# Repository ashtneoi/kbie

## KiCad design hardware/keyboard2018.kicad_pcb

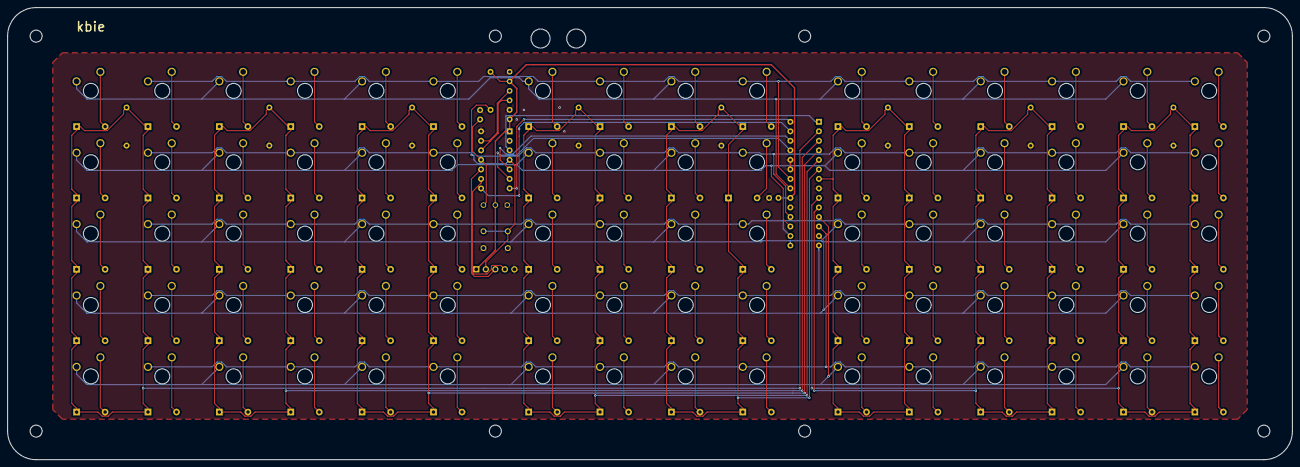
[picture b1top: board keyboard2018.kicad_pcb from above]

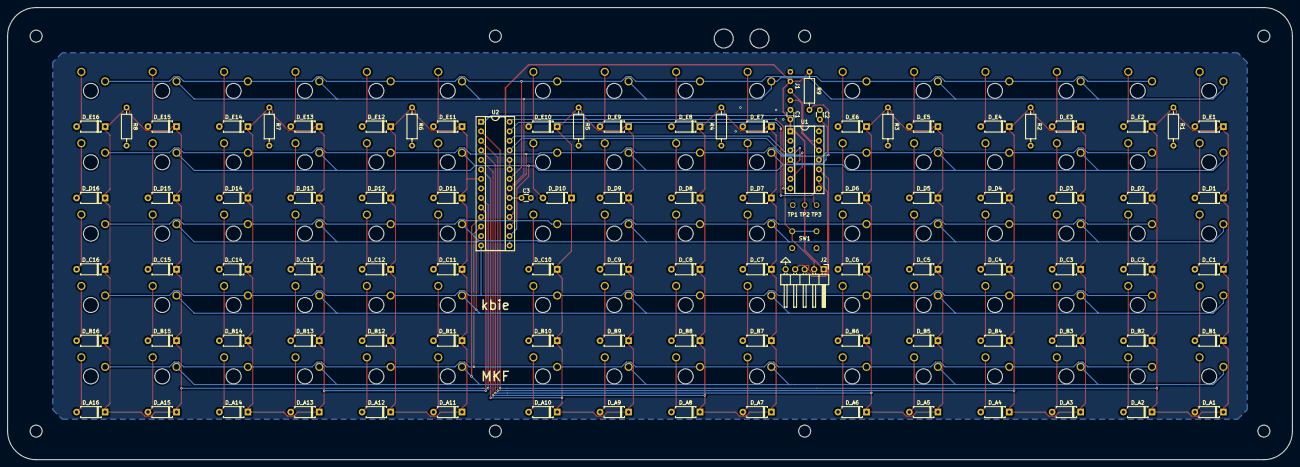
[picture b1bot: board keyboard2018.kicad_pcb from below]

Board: 2 copper layers, 342.9 x 120.7 mm, 180 parts (99 on the bottom side), 111 nets.

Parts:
C1, C3: 100n; C_Disc_D3.0mm_W1.6mm_P2.50mm
C2: 470n; C_Disc_D3.0mm_W1.6mm_P2.50mm
D_A1, D_A2, D_A3, D_A4, D_A5, D_A6, D_A7, D_A8, D_A9, D_A10, D_A11, D_A12, D_A13, D_A14, D_A15, D_A16: D; D_A-405_P7.62mm_Horizontal
D_B1, D_B2, D_B3, D_B4, D_B5, D_B6, D_B7, D_B8, D_B9, D_B10, D_B11, D_B12, D_B13, D_B14, D_B15, D_B16: D; D_A-405_P7.62mm_Horizontal
D_C1, D_C2, D_C3, D_C4, D_C5, D_C6, D_C7, D_C8, D_C9, D_C10, D_C11, D_C12, D_C13, D_C14, D_C15, D_C16: D; D_A-405_P7.62mm_Horizontal
D_D1, D_D2, D_D3, D_D4, D_D5, D_D6, D_D7, D_D8, D_D9, D_D10, D_D11, D_D12, D_D13, D_D14, D_D15, D_D16: D; D_A-405_P7.62mm_Horizontal
D_E1, D_E2, D_E3, D_E4, D_E5, D_E6, D_E7, D_E8, D_E9, D_E10, D_E11, D_E12, D_E13, D_E14, D_E15, D_E16: D; D_A-405_P7.62mm_Horizontal
J1: USB_B_no_shield; captive USB
J2: Conn_01x05_Male; PinHeader_1x05_P2.54mm_Horizontal
R1, R2, R3, R4, R5, R6, R7, R8: 1k; R_Axial_DIN0207_L6.3mm_D2.5mm_P10.16mm_Horizontal
R9: 10k; R_Axial_DIN0207_L6.3mm_D2.5mm_P10.16mm_Horizontal
SW1: SW_Push; TE FSM4JAH
SW_A1, SW_A2, SW_A3, SW_A4, SW_A5, SW_A6, SW_A7, SW_A8, SW_A9, SW_A10, SW_A11, SW_A12, SW_A13, SW_A14, SW_A15, SW_A16: SW_Push; SW_Cherry_MX1A_1.00u_Plate_with_mounting_hole
SW_B1, SW_B2, SW_B3, SW_B4, SW_B5, SW_B6, SW_B7, SW_B8, SW_B9, SW_B10, SW_B11, SW_B12, SW_B13, SW_B14, SW_B15, SW_B16: SW_Push; SW_Cherry_MX1A_1.00u_Plate_with_mounting_hole
SW_C1, SW_C2, SW_C3, SW_C4, SW_C5, SW_C6, SW_C7, SW_C8, SW_C9, SW_C10, SW_C11, SW_C12, SW_C13, SW_C14, SW_C15, SW_C16: SW_Push; SW_Cherry_MX1A_1.00u_Plate_with_mounting_hole
SW_D1, SW_D2, SW_D3, SW_D4, SW_D5, SW_D6, SW_D7, SW_D8, SW_D9, SW_D10, SW_D11, SW_D12, SW_D13, SW_D14, SW_D15, SW_D16: SW_Push; SW_Cherry_MX1A_1.00u_Plate_with_mounting_hole
SW_E1, SW_E2, SW_E3, SW_E4, SW_E5, SW_E6, SW_E7, SW_E8, SW_E9, SW_E10, SW_E11, SW_E12, SW_E13, SW_E14, SW_E15, SW_E16: SW_Push; SW_Cherry_MX1A_1.00u_Plate_with_mounting_hole
TP1, TP2, TP3: TestPoint; test point 1mm
U1: PIC16F1454-IP; DIP-14_W7.62mm_Socket
U2: PIC16F18855-IP; DIP-28_W7.62mm_Socket

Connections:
/COL1: D_A1.1, D_A2.1, D_B1.1, D_B2.1, D_C1.1, D_C2.1, D_D1.1, D_D2.1, D_E1.1, D_E2.1, R1.1, U2.2
/COL2: D_A3.1, D_A4.1, D_B3.1, D_B4.1, D_C3.1, D_C4.1, D_D3.1, D_D4.1, D_E3.1, D_E4.1, R2.1, U2.3
/COL3: D_A5.1, D_A6.1, D_B5.1, D_B6.1, D_C5.1, D_C6.1, D_D5.1, D_D6.1, D_E5.1, D_E6.1, R3.1, U2.4
/COL4: D_A7.1, D_A8.1, D_B7.1, D_B8.1, D_C7.1, D_C8.1, D_D7.1, D_D8.1, D_E7.1, D_E8.1, R4.1, U2.5
/COL5: D_A9.1, D_A10.1, D_B9.1, D_B10.1, D_C9.1, D_C10.1, D_D9.1, D_D10.1, D_E9.1, D_E10.1, R5.1, U2.6
/COL6: D_A11.1, D_A12.1, D_B11.1, D_B12.1, D_C11.1, D_C12.1, D_D11.1, D_D12.1, D_E11.1, D_E12.1, R6.1, U2.7
/COL7: D_A13.1, D_A14.1, D_B13.1, D_B14.1, D_C13.1, D_C14.1, D_D13.1, D_D14.1, D_E13.1, D_E14.1, R7.1, U2.10
/COL8: D_A15.1, D_A16.1, D_B15.1, D_B16.1, D_C15.1, D_C16.1, D_D15.1, D_D16.1, D_E15.1, D_E16.1, R8.1, U2.9
/D+: J1.3, U1.13
/D-: J1.2, U1.12
/ICSPCLK_EXT: J2.4, U1.9
/ICSPCLK_INT: U1.8, U2.27
/ICSPDAT_EXT: J2.3, U1.10
/ICSPDAT_INT: U1.7, U2.28
/ROW1: SW_A1.2, SW_A3.2, SW_A5.2, SW_A7.2, SW_A9.2, SW_A11.2, SW_A13.2, SW_A15.2, U2.11
/ROW2: SW_A2.2, SW_A4.2, SW_A6.2, SW_A8.2, SW_A10.2, SW_A12.2, SW_A14.2, SW_A16.2, U2.12
/ROW3: SW_B1.2, SW_B3.2, SW_B5.2, SW_B7.2, SW_B9.2, SW_B11.2, SW_B13.2, SW_B15.2, U2.13
/ROW4: SW_B2.2, SW_B4.2, SW_B6.2, SW_B8.2, SW_B10.2, SW_B12.2, SW_B14.2, SW_B16.2, U2.14
/ROW5: SW_C1.2, SW_C3.2, SW_C5.2, SW_C7.2, SW_C9.2, SW_C11.2, SW_C13.2, SW_C15.2, U2.15
/ROW6: SW_C2.2, SW_C4.2, SW_C6.2, SW_C8.2, SW_C10.2, SW_C12.2, SW_C14.2, SW_C16.2, U2.16
/ROW7: SW_D1.2, SW_D3.2, SW_D5.2, SW_D7.2, SW_D9.2, SW_D11.2, SW_D13.2, SW_D15.2, U2.17
/ROW8: SW_D2.2, SW_D4.2, SW_D6.2, SW_D8.2, SW_D10.2, SW_D12.2, SW_D14.2, SW_D16.2, U2.18
/ROW9: SW_E1.2, SW_E3.2, SW_E5.2, SW_E7.2, SW_E9.2, SW_E11.2, SW_E13.2, SW_E15.2, U2.21
/ROW10: SW_E2.2, SW_E4.2, SW_E6.2, SW_E8.2, SW_E10.2, SW_E12.2, SW_E14.2, SW_E16.2, U2.22
/U1_RX: U1.5, U2.26
/U1_TX: U1.6, U2.25
/~MCLR~_EXT: J2.2, R9.2, SW1.1, U1.4
/~MCLR~_INT: U1.3, U2.1
GND: C1.1, C2.1, C3.1, J1.4, J2.5, R1.2, R2.2, R3.2, R4.2, R5.2, R6.2, R7.2, R8.2, SW1.2, TP1.1, U1.2, U1.14, U2.8, U2.19, U2.23, U2.24
unnamed: C2.2, TP3.1, U1.11
unnamed: D_A1.2, SW_A1.1
unnamed: D_A2.2, SW_A2.1
unnamed: D_A3.2, SW_A3.1
unnamed: D_A4.2, SW_A4.1
unnamed: D_A5.2, SW_A5.1
unnamed: D_A6.2, SW_A6.1
unnamed: D_A7.2, SW_A7.1
unnamed: D_A8.2, SW_A8.1
unnamed: D_A9.2, SW_A9.1
unnamed: D_A10.2, SW_A10.1
unnamed: D_A11.2, SW_A11.1
unnamed: D_A12.2, SW_A12.1
unnamed: D_A13.2, SW_A13.1
unnamed: D_A14.2, SW_A14.1
unnamed: D_A15.2, SW_A15.1
unnamed: D_A16.2, SW_A16.1
unnamed: D_B1.2, SW_B1.1
unnamed: D_B2.2, SW_B2.1
unnamed: D_B3.2, SW_B3.1
unnamed: D_B4.2, SW_B4.1
unnamed: D_B5.2, SW_B5.1
unnamed: D_B6.2, SW_B6.1
unnamed: D_B7.2, SW_B7.1
unnamed: D_B8.2, SW_B8.1
unnamed: D_B9.2, SW_B9.1
unnamed: D_B10.2, SW_B10.1
unnamed: D_B11.2, SW_B11.1
unnamed: D_B12.2, SW_B12.1
unnamed: D_B13.2, SW_B13.1
unnamed: D_B14.2, SW_B14.1
unnamed: D_B15.2, SW_B15.1
unnamed: D_B16.2, SW_B16.1
unnamed: D_C1.2, SW_C1.1
unnamed: D_C2.2, SW_C2.1
unnamed: D_C3.2, SW_C3.1
unnamed: D_C4.2, SW_C4.1
unnamed: D_C5.2, SW_C5.1
unnamed: D_C6.2, SW_C6.1
unnamed: D_C7.2, SW_C7.1
unnamed: D_C8.2, SW_C8.1
unnamed: D_C9.2, SW_C9.1
unnamed: D_C10.2, SW_C10.1
unnamed: D_C11.2, SW_C11.1
unnamed: D_C12.2, SW_C12.1
unnamed: D_C13.2, SW_C13.1
unnamed: D_C14.2, SW_C14.1
unnamed: D_C15.2, SW_C15.1
unnamed: D_C16.2, SW_C16.1
unnamed: D_D1.2, SW_D1.1
unnamed: D_D2.2, SW_D2.1
unnamed: D_D3.2, SW_D3.1
unnamed: D_D4.2, SW_D4.1
unnamed: D_D5.2, SW_D5.1
unnamed: D_D6.2, SW_D6.1
unnamed: D_D7.2, SW_D7.1
unnamed: D_D8.2, SW_D8.1
unnamed: D_D9.2, SW_D9.1
unnamed: D_D10.2, SW_D10.1
unnamed: D_D11.2, SW_D11.1
unnamed: D_D12.2, SW_D12.1
unnamed: D_D13.2, SW_D13.1
unnamed: D_D14.2, SW_D14.1
unnamed: D_D15.2, SW_D15.1
unnamed: D_D16.2, SW_D16.1
unnamed: D_E1.2, SW_E1.1
unnamed: D_E2.2, SW_E2.1
unnamed: D_E3.2, SW_E3.1
unnamed: D_E4.2, SW_E4.1
unnamed: D_E5.2, SW_E5.1
unnamed: D_E6.2, SW_E6.1
unnamed: D_E7.2, SW_E7.1
unnamed: D_E8.2, SW_E8.1
unnamed: D_E9.2, SW_E9.1
unnamed: D_E10.2, SW_E10.1
unnamed: D_E11.2, SW_E11.1
unnamed: D_E12.2, SW_E12.1
unnamed: D_E13.2, SW_E13.1
unnamed: D_E14.2, SW_E14.1
unnamed: D_E15.2, SW_E15.1
unnamed: D_E16.2, SW_E16.1
VDD: C1.2, C3.2, J1.1, J2.1, R9.1, TP2.1, U1.1, U2.20

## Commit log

2018-09-04 Initial commit (empty)
2018-09-04 Add some PIC asm stuff
2018-09-04 Add hardware files
    Some of them are probably unnecessary but I'll figure it out later.
2018-09-04 Fix backwards key status
2018-09-04 Switch (haha) from F18854 to F18855
2018-09-09 Finish schematic
2018-09-09 Assign a couple more footprints
2018-09-09 Finish schematic again
2018-09-10 Switch USB connector
2018-09-10 Add forgotten footprint
2018-09-10 Decent layout
2018-09-10 Get design rules set up for JLCPCB
    Also make silkscreen text slightly thicker.
2018-09-11 checkpoint reached
2018-09-11 Almost done routing!
2018-09-11 ground planes ground plANES GROUND PLANES GR
2018-09-11 Space holes a bit further out (I think)
2018-09-11 Add some cut lines for laser cutting
2018-09-11 Add comment-less M3 hole footprint
2018-09-11 Forgot the laser kerf is a width, not an offset
2018-09-11 Round out some cuts
2018-09-11 Adjust some mechanical stuff
2018-09-11 Nudge a couple footprints
2018-09-11 Adjust holes, cuts, and edges
    Hopefully this is right.
2018-09-12 Remove keyswitch silkscreen
2018-09-12 I think it's done!
2018-09-12 Move screw hole-to-edge clearances to Dwgs layer
2018-09-12 *Now* we're done
2018-09-12 Add some helpful text
2018-09-12 Separate text so it's easier to select
2018-09-12 Add laser SVG files
2018-09-12 Quick last-minute changes
2018-09-12 Add gerbers and drill files
